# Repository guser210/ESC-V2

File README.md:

# ESC-V2
Full STM32CubeEDI project of the ESC I currently use on my Drones.

You can find more information on the link below,

https://discord.gg/pByahDupYP

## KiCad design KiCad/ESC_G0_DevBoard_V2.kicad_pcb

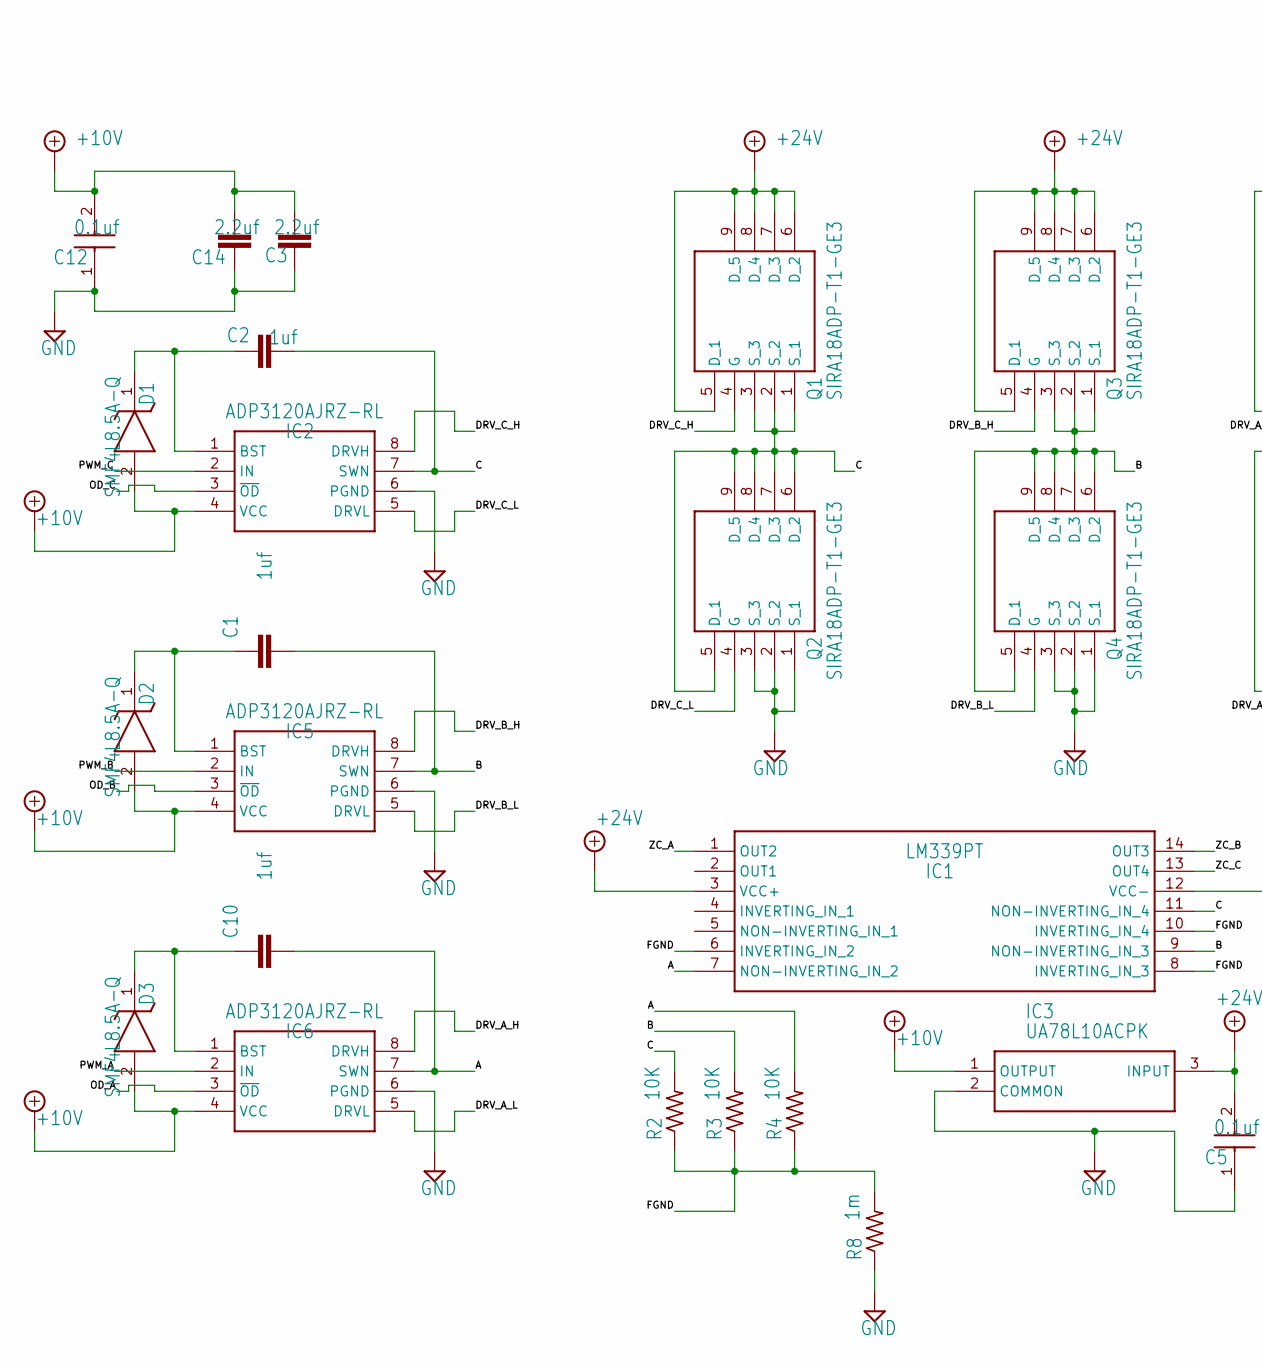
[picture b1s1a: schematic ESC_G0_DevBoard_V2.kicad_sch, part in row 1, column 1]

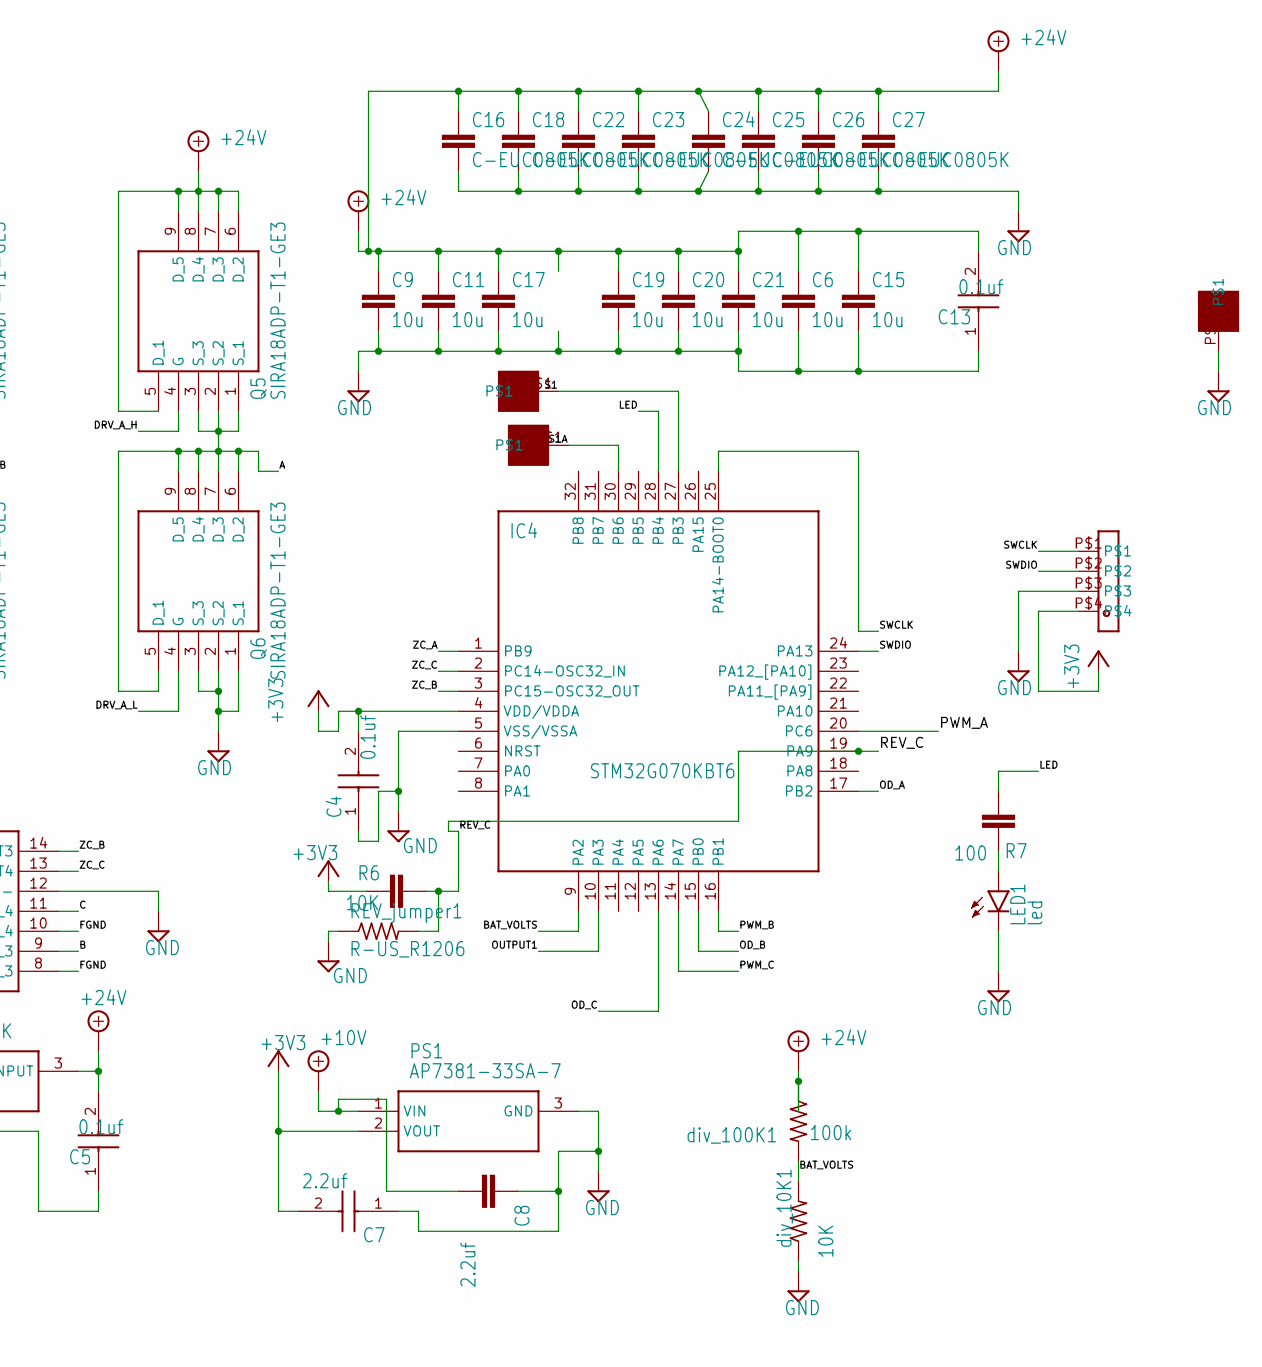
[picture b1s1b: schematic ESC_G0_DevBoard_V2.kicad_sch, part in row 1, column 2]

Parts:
C1, C2, C10: 1uf; C0805K
C3, C8, C14: 2.2uf; C0805K
C4, C5, C12, C13: 0.1uf; CAPC2012X135N
C6, C9, C11, C15, C17, C19, C20, C21: 10u; C1206K
C7: 2.2uf; CAPC2012X135N
C16, C18, C22, C23, C24, C25, C26, C27: C-EUC0805K; C0805K
D1, D2, D3: SMF4L8.5A-Q; SODFL3716X135N
IC1: LM339PT; SOP65P640X120-14N
IC2, IC5, IC6: ADP3120AJRZ-RL; SOIC127P600X175-8N
IC3: UA78L10ACPK; PK(R-PSSO-F3)
IC4: STM32G070KBT6; QFP80P900X900X160-32N
LED1: led; SML0805
PS1: AP7381-33SA-7; SOT96P240X120-3N
Q1, Q2, Q3, Q4, Q5, Q6: SIRA18ADP-T1-GE3; SIRA18ADPT1GE3
R2, R3, R4: 10K; R0603
R6: 10K; C0805K
R7: 100; C0805K
R8: 1m; R0603
REV_jumper1: R-US_R1206; R1206
U$1, U$2, U$3: 3X3_PAD
U$4: STLINK_HEADER
div_10K1: 10K; R0603
div_100K1: 100k; R0603

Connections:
+3V3: C4.2, C7.2, IC4.4 (VDD/VDDA), PS1.2 (VOUT), R6.2, U$4.P$4
+10V: C3.2, C8.2, C12.2, C14.2, D1.2 (A), D2.2 (A), D3.2 (A), IC2.4 (VCC), IC3.1 (OUTPUT), IC5.4 (VCC), IC6.4 (VCC), PS1.1 (VIN)
+24V: C5.2, C6.1, C9.1, C11.1, C13.2, C15.1, C16.1, C17.1, C18.1, C19.1, C20.1, C21.1, C22.1, C23.1, C24.1, C25.1, C26.1, C27.1, IC1.3 (VCC+), IC3.3 (INPUT), Q1.5 (D_1), Q1.6 (D_2), Q1.7 (D_3), Q1.8 (D_4), Q1.9 (D_5), Q3.5 (D_1), Q3.6 (D_2), Q3.7 (D_3), Q3.8 (D_4), Q3.9 (D_5), Q5.5 (D_1), Q5.6 (D_2), Q5.7 (D_3), Q5.8 (D_4), Q5.9 (D_5), div_100K1.1
/A: C10.2, IC1.7 (NON-INVERTING_IN_2), IC6.7 (SWN), Q5.1 (S_1), Q5.2 (S_2), Q5.3 (S_3), Q6.5 (D_1), Q6.6 (D_2), Q6.7 (D_3), Q6.8 (D_4), Q6.9 (D_5), R4.2; also elsewhere on the board
/B: C1.2, IC1.9 (NON-INVERTING_IN_3), IC5.7 (SWN), Q3.1 (S_1), Q3.2 (S_2), Q3.3 (S_3), Q4.5 (D_1), Q4.6 (D_2), Q4.7 (D_3), Q4.8 (D_4), Q4.9 (D_5), R3.2; also elsewhere on the board
/BAT_VOLTS: IC4.9 (PA2), div_10K1.2, div_100K1.2
/C: C2.2, IC1.11 (NON-INVERTING_IN_4), IC2.7 (SWN), Q1.1 (S_1), Q1.2 (S_2), Q1.3 (S_3), Q2.5 (D_1), Q2.6 (D_2), Q2.7 (D_3), Q2.8 (D_4), Q2.9 (D_5), R2.2; also elsewhere on the board
/DRV_A_H: IC6.8 (DRVH), Q5.4 (G)
/DRV_A_L: IC6.5 (DRVL), Q6.4 (G)
/DRV_B_H: IC5.8 (DRVH), Q3.4 (G)
/DRV_B_L: IC5.5 (DRVL), Q4.4 (G)
/DRV_C_H: IC2.8 (DRVH), Q1.4 (G)
/DRV_C_L: IC2.5 (DRVL), Q2.4 (G)
/FGND: IC1.6 (INVERTING_IN_2), IC1.8 (INVERTING_IN_3), IC1.10 (INVERTING_IN_4), R2.1, R3.1, R4.1, R8.2
/LED: IC4.28 (PB4), R7.2
/OD_A: IC4.17 (PB2), IC6.3 (~OD)
/OD_B: IC4.15 (PB0), IC5.3 (~OD)
/OD_C: IC2.3 (~OD), IC4.13 (PA6)
/OUTPUT1: IC4.10 (PA3)
/PWM_A: IC4.20 (PC6), IC6.2 (IN)
/PWM_B: IC4.16 (PB1), IC5.2 (IN)
/PWM_C: IC2.2 (IN), IC4.14 (PA7)
/REV_C: IC4.19 (PA9), R6.1, REV_jumper1.2
/S1: IC4.27 (PB3), U$1.P$1
/S1A: IC4.30 (PB6), U$2.P$1
/SWCLK: IC4.25 (PA14-BOOT0), U$4.P$1
/SWDIO: IC4.24 (PA13), U$4.P$2
/ZC_A: IC1.1 (OUT2), IC4.1 (PB9)
/ZC_B: IC1.14 (OUT3), IC4.3 (PC15-OSC32_OUT)
/ZC_C: IC1.13 (OUT4), IC4.2 (PC14-OSC32_IN)
GND: C3.1, C4.1, C5.1, C6.2, C7.1, C8.1, C9.2, C11.2, C12.1, C13.1, C14.1, C15.2, C16.2, C17.2, C18.2, C19.2, C20.2, C21.2, C22.2, C23.2, C24.2, C25.2, C26.2, C27.2, IC1.12 (VCC-), IC2.6 (PGND), IC3.2 (COMMON), IC3.4, IC4.5 (VSS/VSSA), IC5.6 (PGND), IC6.6 (PGND), LED1.C, PS1.3 (GND), Q2.1 (S_1), Q2.2 (S_2), Q2.3 (S_3), Q4.1 (S_1), Q4.2 (S_2), Q4.3 (S_3), Q6.1 (S_1), Q6.2 (S_2), Q6.3 (S_3), R8.1, REV_jumper1.1, U$3.P$1, U$4.P$3, div_10K1.1
unnamed 31: C1.1, D2.1 (K), IC5.1 (BST); also elsewhere on the board
unnamed 32: C2.1, D1.1 (K), IC2.1 (BST); also elsewhere on the board
unnamed 33: C10.1, D3.1 (K), IC6.1 (BST); also elsewhere on the board
unnamed: LED1.A, R7.1

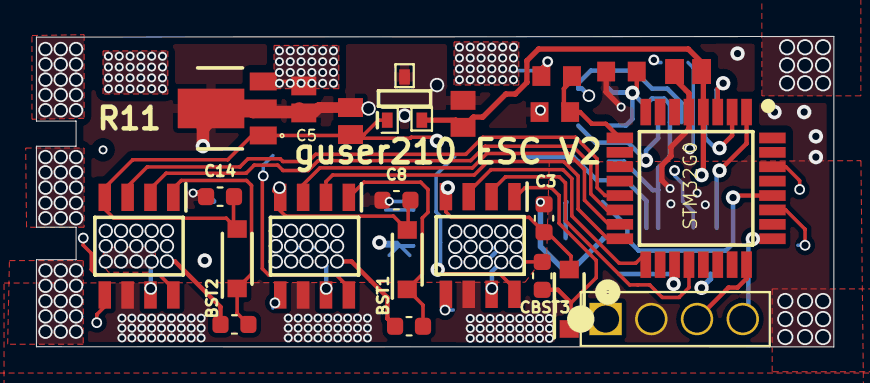
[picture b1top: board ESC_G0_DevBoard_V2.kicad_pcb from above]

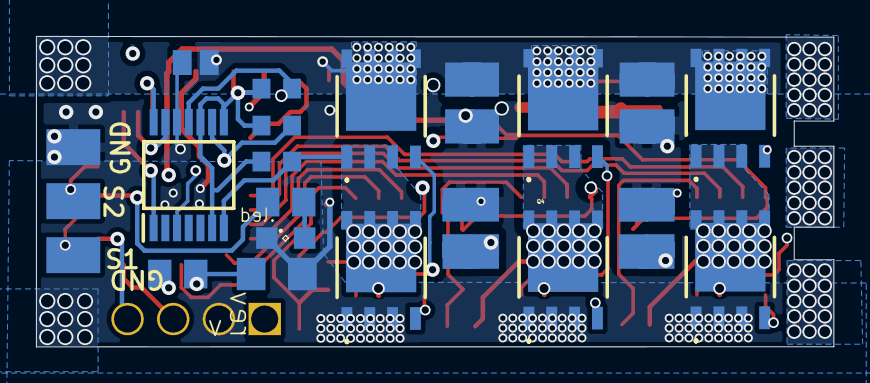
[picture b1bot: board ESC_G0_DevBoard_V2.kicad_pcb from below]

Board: 8 copper layers, 44.3 x 17.2 mm, 57 parts (34 on the bottom side), 34 nets.

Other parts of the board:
BST1, BST2: 1uf; C_0603_1608Metric
CBST3: 1uf; C_0603_1608Metric

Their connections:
/A: CBST3.2; also elsewhere on the board
/B: BST1.2; also elsewhere on the board
/C: BST2.2; also elsewhere on the board
unnamed 31: BST1.1; also elsewhere on the board
unnamed 32: BST2.1; also elsewhere on the board
unnamed 33: CBST3.1; also elsewhere on the board

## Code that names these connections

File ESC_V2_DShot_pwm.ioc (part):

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Mcu.Name=STM32G070KBTx
Mcu.Package=LQFP32
Mcu.UserName=STM32G070KBTx
PA13.Mode=Serial_Wire
PA13.Signal=SYS_SWDIO
PA14-BOOT0.Mode=Serial_Wire
PA14-BOOT0.Signal=SYS_SWCLK
PA2.GPIOParameters=GPIO_Label
PA2.GPIO_Label=BAT_VOLTS
PA2.Mode=IN2
PA2.Signal=ADC1_IN2
PA6.GPIOParameters=GPIO_Speed,GPIO_PuPd,GPIO_Label
PA6.GPIO_Label=OD_C
PA6.GPIO_PuPd=GPIO_PULLDOWN
PA6.GPIO_Speed=GPIO_SPEED_FREQ_MEDIUM
PA6.Signal=GPIO_Output
PA7.GPIOParameters=GPIO_PuPd,GPIO_Label
PA7.GPIO_Label=PWM_C
PA7.GPIO_PuPd=GPIO_PULLDOWN
PA7.Signal=S_TIM3_CH2
PA9.GPIOParameters=GPIO_PuPd,GPIO_Label
PA9.GPIO_Label=REV
PA9.GPIO_PuPd=GPIO_PULLUP
PA9.Signal=GPIO_Input
PB0.GPIOParameters=GPIO_Speed,GPIO_PuPd,GPIO_Label
PB0.GPIO_Label=OD_B
PB0.GPIO_PuPd=GPIO_PULLDOWN
PB0.GPIO_Speed=GPIO_SPEED_FREQ_MEDIUM
PB0.Signal=GPIO_Output
PB1.GPIOParameters=GPIO_PuPd,GPIO_Label
PB1.GPIO_Label=PWM_B
PB1.GPIO_PuPd=GPIO_PULLDOWN
PB1.Signal=S_TIM3_CH4
PB2.GPIOParameters=GPIO_Speed,GPIO_PuPd,GPIO_Label
PB2.GPIO_Label=OD_A
PB2.GPIO_PuPd=GPIO_PULLDOWN
PB2.GPIO_Speed=GPIO_SPEED_FREQ_MEDIUM
PB2.Signal=GPIO_Output
PB3.GPIOParameters=GPIO_Speed,GPIO_Label
PB3.GPIO_Label=signal
PB3.GPIO_Speed=GPIO_SPEED_FREQ_VERY_HIGH
PB3.Signal=GPIO_Output
PB4.GPIOParameters=GPIO_Speed,GPIO_Label
PB4.GPIO_Label=LED
PB4.GPIO_Speed=GPIO_SPEED_FREQ_MEDIUM
PB4.Signal=GPIO_Output
PB6.GPIOParameters=GPIO_FM6,GPIO_Speed,GPIO_PuPd,GPIO_Label
PB6.GPIO_FM6=SYSCFG_FASTMODEPLUS_PB6
PB6.GPIO_Label=Proshot
PB6.GPIO_PuPd=GPIO_NOPULL
PB6.GPIO_Speed=GPIO_SPEED_FREQ_VERY_HIGH
PB6.Signal=S_TIM1_CH3
PB9.GPIOParameters=GPIO_PuPd,GPIO_Label,GPIO_ModeDefaultEXTI
PB9.GPIO_Label=ZC_A
PB9.GPIO_ModeDefaultEXTI=GPIO_MODE_IT_FALLING
PB9.GPIO_PuPd=GPIO_PULLUP
PB9.Signal=GPXTI9
PC14-OSC32_IN\ (PC14).GPIOParameters=GPIO_PuPd,GPIO_Label,GPIO_ModeDefaultEXTI
PC14-OSC32_IN\ (PC14).GPIO_Label=ZC_C
PC14-OSC32_IN\ (PC14).GPIO_ModeDefaultEXTI=GPIO_MODE_IT_FALLING
PC14-OSC32_IN\ (PC14).GPIO_PuPd=GPIO_PULLUP
PC14-OSC32_IN\ (PC14).Signal=GPXTI14
PC15-OSC32_OUT\ (PC15).GPIOParameters=GPIO_PuPd,GPIO_Label,GPIO_ModeDefaultEXTI
PC15-OSC32_OUT\ (PC15).GPIO_Label=ZC_B
PC15-OSC32_OUT\ (PC15).GPIO_ModeDefaultEXTI=GPIO_MODE_IT_FALLING
PC15-OSC32_OUT\ (PC15).GPIO_PuPd=GPIO_PULLUP
PC15-OSC32_OUT\ (PC15).Signal=GPXTI15
PC6.GPIOParameters=GPIO_PuPd,GPIO_Label
PC6.GPIO_Label=PWM_A
PC6.GPIO_PuPd=GPIO_PULLDOWN
PC6.Signal=S_TIM3_CH1
RCC.HSE_VALUE=8000000
RCC.SYSCLKFreq_VALUE=64000000
RCC.SYSCLKSource=RCC_SYSCLKSOURCE_PLLCLK
board=custom

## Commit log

2023-08-10 Base upload
2023-08-10 Upload 1
2023-08-10 PCB files
